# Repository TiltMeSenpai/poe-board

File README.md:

# Unnamed PoE LED Driver

## Status: UNTESTED

Hub75 LED Panel driver + 10/100 Base T to MII transciever + 25W PoE supply.  
Board is untested, estimated driver logic power consumption is ~250-500ma (hopefully less).  
Remaining 4-ish amps should be enough to drive 64x64 panel at full brightness, however, with
a 1oz copper board, this will (in theory) induce a ~20C temp rise.

## Basic Stats

| Stat | Value |
|---|---|
| Voltage  | 5v  |
| Amperage | ~5A |
| Onboard current draw | TBD (Hopefully under 500ma) |
| Interface | 10/100 base T transciever, 4 debug LED's, Hub75 header |

## Board stats

| Stat | Value |
|---|---|
| Layers             |            4 |
| Min Trace Width    |        6 mil |
| Min Trace Spacing  |        5 mil |
| Min Drill Size     |       10 mil |
| Min Via Annulus    |        5 mil |
| Min Total Via Size |       20 mil |
| Blind/Buried Vias  |           No |
| Impedence Control  |           No |
| Copper Weight      | 2 oz/Default |

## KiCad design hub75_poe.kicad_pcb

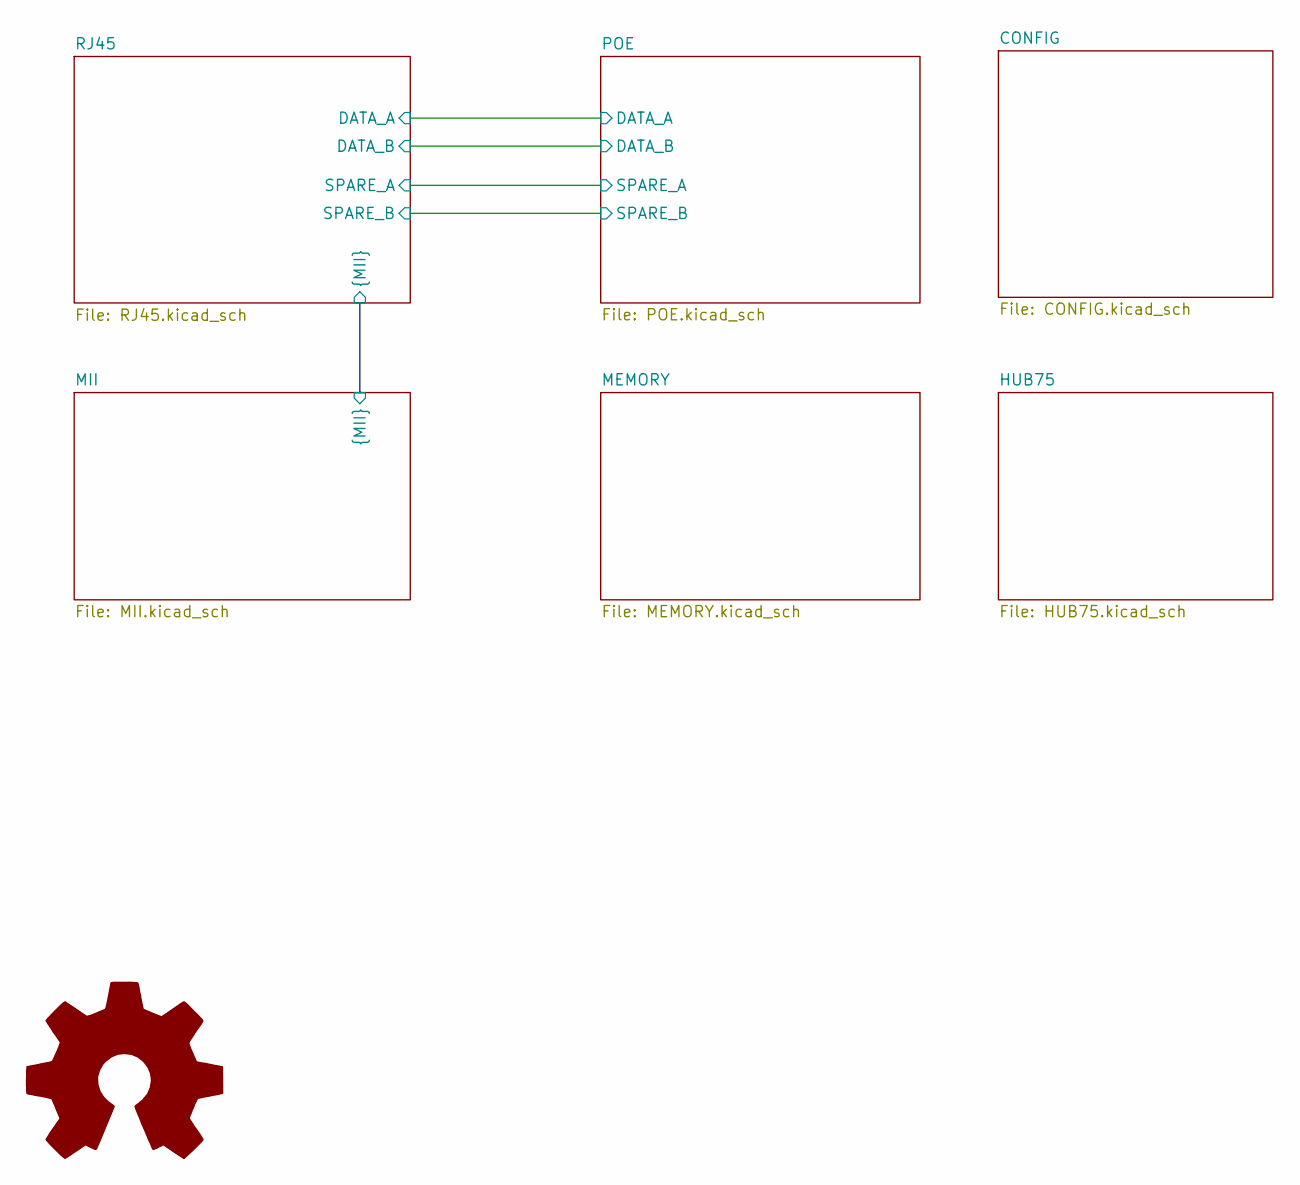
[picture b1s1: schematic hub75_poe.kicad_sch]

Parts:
S1: Logo_Open_Hardware_Large; OSHW-Symbol_6.7x6mm_SilkScreen

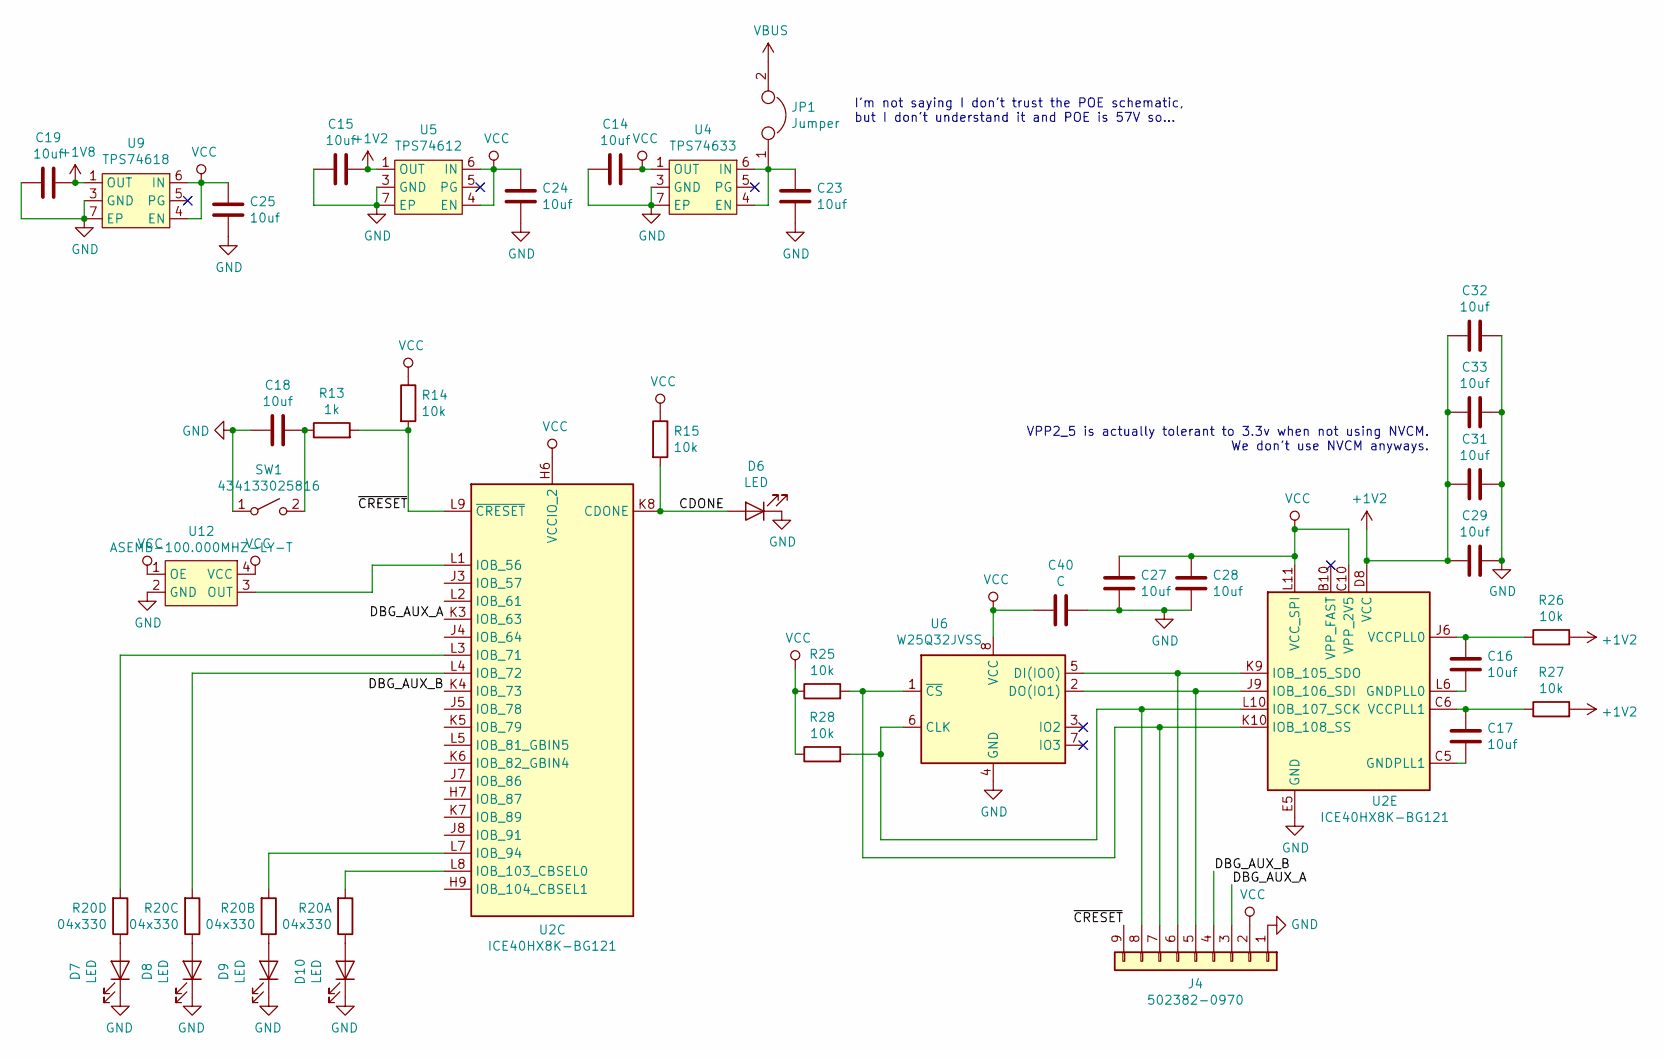
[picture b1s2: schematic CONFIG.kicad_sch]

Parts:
C14, C15, C16, C17, C19, C23, C24, C25, C27, C28, C29, C31, C32, C33: 10uf; C_0402_1005Metric
C18: 10uf; C_0805_2012Metric
C40: C; C_0402_1005Metric
D6, D7, D8, D9, D10: LED; D_0805_2012Metric_Castellated
J4: 502382-0970; Molex_CLIK-Mate_502382-0970_1x09-1MP_P1.25mm_Vertical
JP1: Jumper; PinSocket_1x02_P1.27mm_Vertical
R13: 1k; R_0402_1005Metric
R14, R15, R25, R26, R27, R28: 10k; R_0402_1005Metric
R20: 04x330; R_Array_Convex_4x0612
SW1: 434133025816; SW_Push_1P1T_NO_Vertical_Wuerth_434133025816
U2: ICE40HX8K-BG121; BGA-121_9.0x9.0mm_Layout11x11_P0.8mm_Ball0.4mm_Pad0.35mm_NS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
U4: TPS74633; WSON-6-1EP_2x2mm_P0.65mm_EP1x1.6mm
U5: TPS74612; WSON-6-1EP_2x2mm_P0.65mm_EP1x1.6mm
U6: W25Q32JVSS; SOIC-8_5.23x5.23mm_P1.27mm
U9: TPS74618; WSON-6-1EP_2x2mm_P0.65mm_EP1x1.6mm
U12: ASEMB-100.000MHZ-LY-T; SOIC-4

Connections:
+1V2: C15.2, C29.1, C31.1, C32.1, C33.1, R26.2, R27.2, U2.D4 (VCC), U2.D8 (VCC), U2.H4 (VCC), U2.H8 (VCC), U5.1 (OUT)
+1V8: C19.2, U9.1 (OUT); also elsewhere on the board
/CONFIG/CDONE: D6.2 (A), R15.2, U2.K8 (CDONE)
/CONFIG/DBG_AUX_A: J4.3, U2.K3 (IOB_63)
/CONFIG/DBG_AUX_B: J4.4, U2.K4 (IOB_73)
/CONFIG/~CRESET: J4.9, R13.2, R14.2, U2.L9 (~CRESET)
GND: C14.1, C15.1, C18.1, C19.1, C23.2, C24.2, C25.2, C27.1, C28.1, C29.2, C31.2, C32.2, C33.2, C40.2, D6.1 (K), D7.1 (K), D8.1 (K), D9.1 (K), D10.1 (K), J4.1, SW1.1 (A), U2.E5 (GND), U2.E6 (GND), U2.E7 (GND), U2.F5 (GND), U2.F6 (GND), U2.F7 (GND), U2.G5 (GND), U2.G6 (GND), U2.G7 (GND), U2.H5 (GND), U4.3 (GND), U4.7 (EP), U5.3 (GND), U5.7 (EP), U6.4 (GND), U9.3 (GND), U9.7 (EP), U12.2 (GND); also elsewhere on the board
unnamed: C16.1, R26.1, U2.J6 (VCCPLL0)
unnamed: C16.2, U2.L6 (GNDPLL0)
unnamed: C17.1, R27.1, U2.C6 (VCCPLL1)
unnamed: C17.2, U2.C5 (GNDPLL1)
unnamed: C18.2, R13.1, SW1.2 (B)
unnamed: C23.1, JP1.1, U4.4 (EN), U4.6 (IN)
unnamed: D7.2 (A), R20.5
unnamed: D8.2 (A), R20.6
unnamed: D9.2 (A), R20.7
unnamed: D10.2 (A), R20.8
unnamed: J4.5, U2.J9 (IOB_106_SDI), U6.2 (DO(IO1))
unnamed: J4.6, U2.K9 (IOB_105_SDO), U6.5 (DI(IO0))
unnamed: J4.7, R25.2, U2.K10 (IOB_108_SS), U6.1 (~CS)
unnamed: J4.8, R28.2, U2.L10 (IOB_107_SCK), U6.6 (CLK)
unnamed: R20.1, U2.L8 (IOB_103_CBSEL0)
unnamed: R20.2, U2.L7 (IOB_94)
unnamed: R20.3, U2.L4 (IOB_72)
unnamed: R20.4, U2.L3 (IOB_71)
unnamed: U2.L1 (IOB_56), U12.3 (OUT)
VBUS: JP1.2; also elsewhere on the board
VCC: C14.2, C24.1, C25.1, C27.2, C28.2, C40.1, J4.2, R14.1, R15.1, R25.1, R28.1, U2.C10 (VPP_2V5), U2.H6 (VCCIO_2), U2.L11 (VCC_SPI), U4.1 (OUT), U5.4 (EN), U5.6 (IN), U6.8 (VCC), U9.4 (EN), U9.6 (IN), U12.1 (OE), U12.4 (VCC); also elsewhere on the board

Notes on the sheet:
I'm not saying I don't trust the POE schematic, but I don't understand it and POE is 57V so...
VPP2_5 is actually tolerant to 3.3v when not using NVCM. We don't use NVCM anyways.

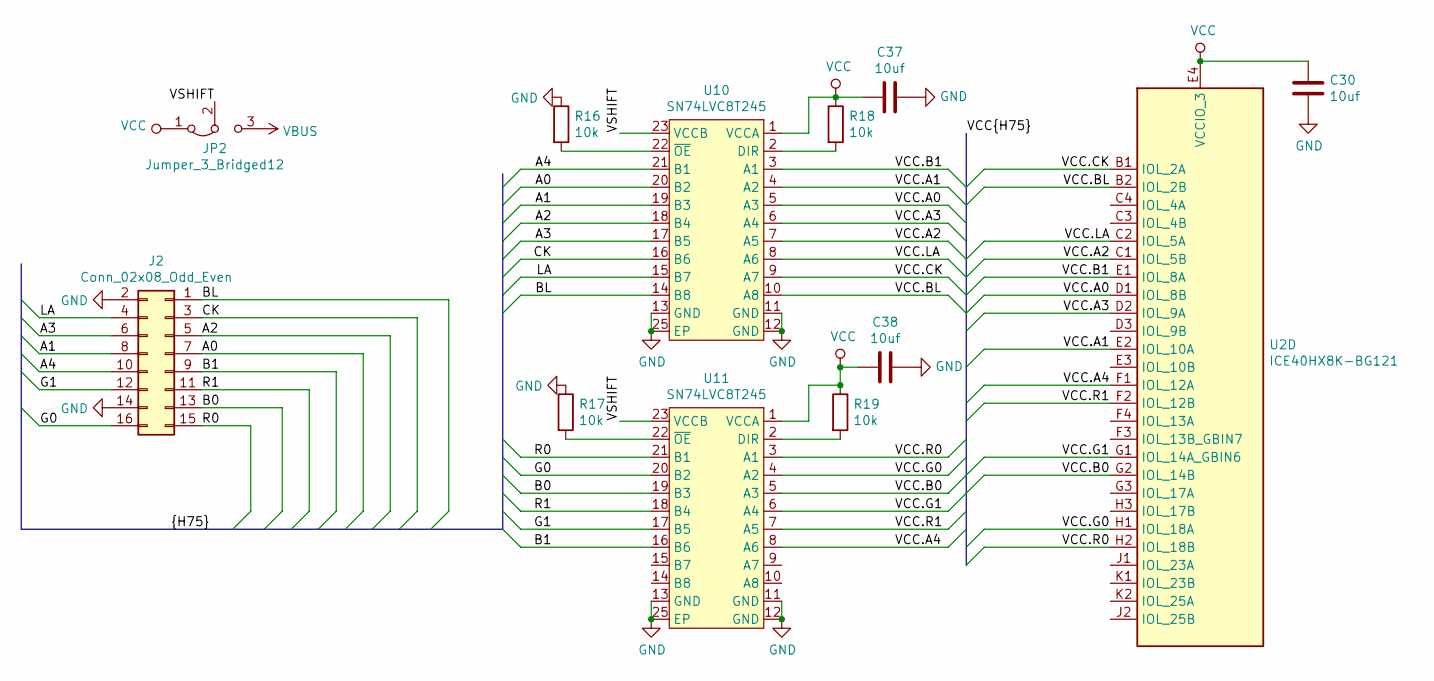
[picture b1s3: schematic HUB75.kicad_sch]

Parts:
C30, C37, C38: 10uf; C_0402_1005Metric
J2: Conn_02x08_Odd_Even; PinSocket_2x08_P2.54mm_Vertical
JP2: Jumper_3_Bridged12; PinHeader_1x03_P1.27mm_Vertical
R16, R17, R18, R19: 10k; R_0402_1005Metric
U2: ICE40HX8K-BG121; BGA-121_9.0x9.0mm_Layout11x11_P0.8mm_Ball0.4mm_Pad0.35mm_NS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
U10, U11: SN74LVC8T245

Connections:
/HUB75/A0: J2.7, U10.20 (B2)
/HUB75/A1: J2.8, U10.19 (B3)
/HUB75/A2: J2.5, U10.18 (B4)
/HUB75/A3: J2.6, U10.17 (B5)
/HUB75/A4: J2.10, U10.21 (B1)
/HUB75/B0: J2.13, U11.19 (B3)
/HUB75/B1: J2.9, U11.16 (B6)
/HUB75/BL: J2.1, U10.14 (B8)
/HUB75/CK: J2.3, U10.16 (B6)
/HUB75/G0: J2.16, U11.20 (B2)
/HUB75/G1: J2.12, U11.17 (B5)
/HUB75/LA: J2.4, U10.15 (B7)
/HUB75/R0: J2.15, U11.21 (B1)
/HUB75/R1: J2.11, U11.18 (B4)
/HUB75/VCC.A0: U2.D1 (IOL_8B), U10.5 (A3)
/HUB75/VCC.A1: U2.E2 (IOL_10A), U10.4 (A2)
/HUB75/VCC.A2: U2.C1 (IOL_5B), U10.7 (A5)
/HUB75/VCC.A3: U2.D2 (IOL_9A), U10.6 (A4)
/HUB75/VCC.A4: U2.F1 (IOL_12A), U11.8 (A6)
/HUB75/VCC.B0: U2.G2 (IOL_14B), U11.5 (A3)
/HUB75/VCC.B1: U2.E1 (IOL_8A), U10.3 (A1)
/HUB75/VCC.BL: U2.B2 (IOL_2B), U10.10 (A8)
/HUB75/VCC.CK: U2.B1 (IOL_2A), U10.9 (A7)
/HUB75/VCC.G0: U2.H1 (IOL_18A), U11.4 (A2)
/HUB75/VCC.G1: U2.G1 (IOL_14A_GBIN6), U11.6 (A4)
/HUB75/VCC.LA: U2.C2 (IOL_5A), U10.8 (A6)
/HUB75/VCC.R0: U2.H2 (IOL_18B), U11.3 (A1)
/HUB75/VCC.R1: U2.F2 (IOL_12B), U11.7 (A5)
/HUB75/VSHIFT: JP2.2 (C), U10.23 (VCCB), U10.24 (VCCB), U11.23 (VCCB), U11.24 (VCCB)
GND: C30.2, C37.2, C38.2, J2.2, J2.14, R16.1, R17.1, U10.11 (GND), U10.12 (GND), U10.13 (GND), U10.25 (EP), U11.11 (GND), U11.12 (GND), U11.13 (GND), U11.25 (EP); also elsewhere on the board
unnamed: R16.2, U10.22 (~OE)
unnamed: R17.2, U11.22 (~OE)
unnamed: R18.2, U10.2 (DIR)
unnamed: R19.2, U11.2 (DIR)
VBUS: JP2.3 (B); also elsewhere on the board
VCC: C30.1, C37.1, C38.1, JP2.1 (A), R18.1, R19.1, U2.E4 (VCCIO_3), U2.G4 (VCCIO_3), U10.1 (VCCA), U11.1 (VCCA); also elsewhere on the board

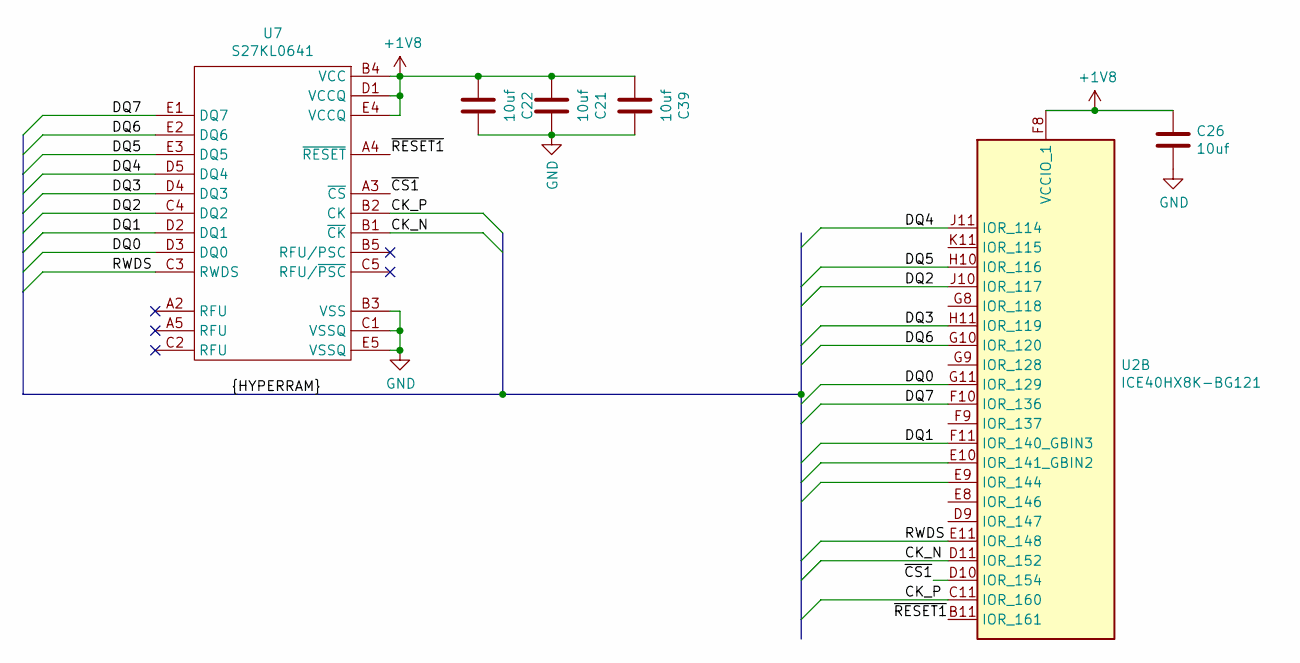
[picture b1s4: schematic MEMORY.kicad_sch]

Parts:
C21, C22, C26, C39: 10uf; C_0402_1005Metric
U2: ICE40HX8K-BG121; BGA-121_9.0x9.0mm_Layout11x11_P0.8mm_Ball0.4mm_Pad0.35mm_NS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
U7: S27KL0641; BGA-24_5x5_6.0x8.0mm

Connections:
+1V8: C21.1, C22.1, C26.1, C39.1, U2.F8 (VCCIO_1), U7.B4 (VCC), U7.D1 (VCCQ), U7.E4 (VCCQ); also elsewhere on the board
/MEMORY/CK_N: U2.D11 (IOR_152), U7.B1 (~CK)
/MEMORY/CK_P: U2.C11 (IOR_160), U7.B2 (CK)
/MEMORY/DQ0: U2.G11 (IOR_129), U7.D3 (DQ0)
/MEMORY/DQ1: U2.F11 (IOR_140_GBIN3), U7.D2 (DQ1)
/MEMORY/DQ2: U2.J10 (IOR_117), U7.C4 (DQ2)
/MEMORY/DQ3: U2.H11 (IOR_119), U7.D4 (DQ3)
/MEMORY/DQ4: U2.J11 (IOR_114), U7.D5 (DQ4)
/MEMORY/DQ5: U2.H10 (IOR_116), U7.E3 (DQ5)
/MEMORY/DQ6: U2.G10 (IOR_120), U7.E2 (DQ6)
/MEMORY/DQ7: U2.F10 (IOR_136), U7.E1 (DQ7)
/MEMORY/RWDS: U2.E11 (IOR_148), U7.C3 (RWDS)
/MEMORY/~CS1: U2.D10 (IOR_154), U7.A3 (~CS)
/MEMORY/~RESET1: U2.B11 (IOR_161), U7.A4 (~RESET)
GND: C21.2, C22.2, C26.2, C39.2, U7.B3 (VSS), U7.C1 (VSSQ), U7.E5 (VSSQ); also elsewhere on the board

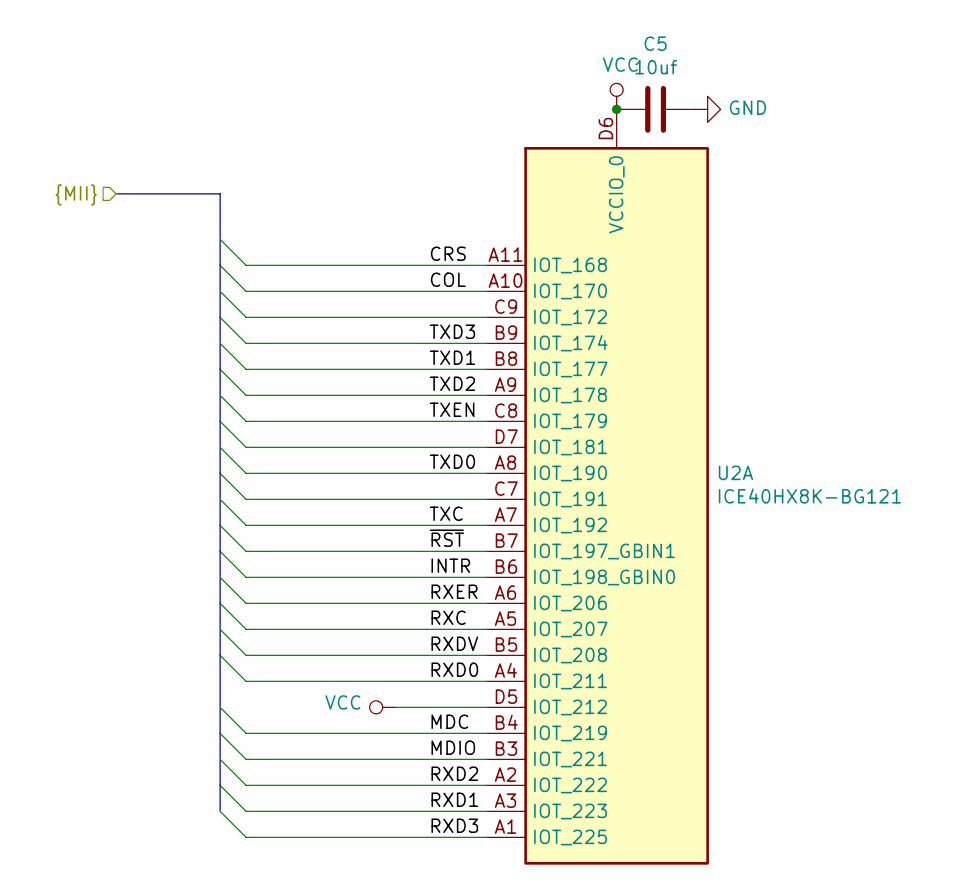
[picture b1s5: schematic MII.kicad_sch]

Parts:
C5: 10uf; C_0402_1005Metric
U2: ICE40HX8K-BG121; BGA-121_9.0x9.0mm_Layout11x11_P0.8mm_Ball0.4mm_Pad0.35mm_NS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

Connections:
/COL: U2.A10 (IOT_170); also elsewhere on the board
/CRS: U2.A11 (IOT_168); also elsewhere on the board
/INTR: U2.B6 (IOT_198_GBIN0); also elsewhere on the board
/MDC: U2.B4 (IOT_219); also elsewhere on the board
/MDIO: U2.B3 (IOT_221); also elsewhere on the board
/RXC: U2.A5 (IOT_207); also elsewhere on the board
/RXD0: U2.A4 (IOT_211); also elsewhere on the board
/RXD1: U2.A3 (IOT_223); also elsewhere on the board
/RXD2: U2.A2 (IOT_222); also elsewhere on the board
/RXD3: U2.A1 (IOT_225); also elsewhere on the board
/RXDV: U2.B5 (IOT_208); also elsewhere on the board
/RXER: U2.A6 (IOT_206); also elsewhere on the board
/TXC: U2.A7 (IOT_192); also elsewhere on the board
/TXD0: U2.A8 (IOT_190); also elsewhere on the board
/TXD1: U2.B8 (IOT_177); also elsewhere on the board
/TXD2: U2.A9 (IOT_178); also elsewhere on the board
/TXD3: U2.B9 (IOT_174); also elsewhere on the board
/TXEN: U2.C8 (IOT_179); also elsewhere on the board
/~RST: U2.B7 (IOT_197_GBIN1); also elsewhere on the board
GND: C5.2; also elsewhere on the board
VCC: C5.1, U2.D5 (IOT_212), U2.D6 (VCCIO_0); also elsewhere on the board

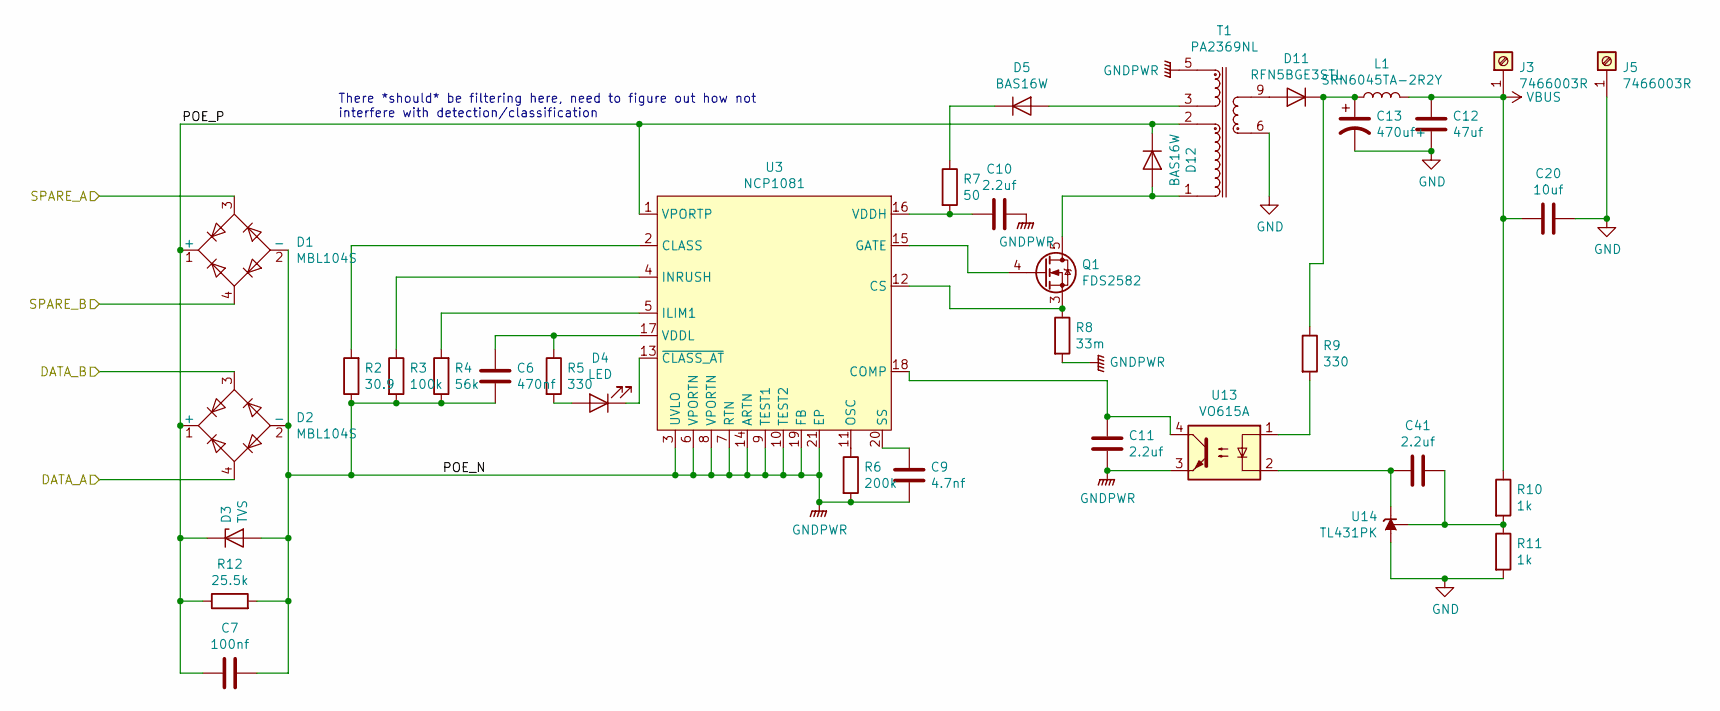
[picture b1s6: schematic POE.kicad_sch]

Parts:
C6: 470nf; C_0402_1005Metric
C7: 100nf; C_0805_2012Metric
C9: 4.7nf; C_0402_1005Metric
C10, C11, C41: 2.2uf; C_0402_1005Metric
C12: 47uf; C_0805_2012Metric
C13: 470uf+; CP_Elec_8x10
C20: 10uf; C_0805_2012Metric
D1, D2: MBL104S; Diode_Bridge_Vishay_MBLS
D3: TVS; D_SMA
D4: LED; D_0805_2012Metric_Castellated
D5, D12: BAS16W; SOT-323_SC-70
D11: RFN5BGE3STL; TO-252-2
J3, J5: 7466003R
L1: SRN6045TA-2R2Y; L_Bourns_SRN6045TA
Q1: FDS2582; SOP-8_3.9x4.9mm_P1.27mm
R2: 30.9; R_0402_1005Metric
R3: 100k; R_0402_1005Metric
R4: 56k; R_0402_1005Metric
R5, R9: 330; R_0402_1005Metric
R6: 200k; R_0402_1005Metric
R7: 50; R_0402_1005Metric
R8: 33m; R_2512_6332Metric
R10, R11: 1k; R_0402_1005Metric
R12: 25.5k; R_0805_2012Metric
T1: PA2369NL
U3: NCP1081; HTSSOP-20-1EP_4.4x6.5mm_P0.65mm_EP3.4x6.5mm
U13: VO615A; VO615A-9X017T
U14: TL431PK; SOT-89-3

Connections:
/DATA_A: D2.4 (~~); also elsewhere on the board
/DATA_B: D2.3 (~~); also elsewhere on the board
/POE/POE_P: C7.1, D1.1 (+), D2.1 (+), D3.1 (A1), D12.3 (K), R12.1, T1.2, U3.1 (VPORTP)
/SPARE_A: D1.3 (~~); also elsewhere on the board
/SPARE_B: D1.4 (~~); also elsewhere on the board
GND: C12.2, C13.2, C20.2, J5.1, R11.2, T1.6, T1.7, U14.2 (A); also elsewhere on the board
GNDPWR: C6.2, C7.2, C9.2, C10.2, C11.2, D1.2 (-), D2.2 (-), D3.2 (A2), R2.1, R3.2, R4.1, R6.2, R8.2, R12.2, T1.5, U3.3 (UVLO), U3.6 (VPORTN), U3.7 (RTN), U3.8 (VPORTN), U3.9 (TEST1), U3.10 (TEST2), U3.14 (ARTN), U3.19 (FB), U3.21 (EP), U13.3; also elsewhere on the board
unnamed: C6.1, R5.1, U3.17 (VDDL)
unnamed: C9.1, U3.20 (SS)
unnamed: C10.1, R7.2, U3.16 (VDDH)
unnamed: C11.1, U3.18 (COMP), U13.4
unnamed: C13.1, D11.2 (K), L1.1, R9.1
unnamed: C41.1, U13.2, U14.3 (K)
unnamed: C41.2, R10.2, R11.1, U14.1 (REF)
unnamed: D4.1 (K), U3.13 (~CLASS_AT)
unnamed: D4.2 (A), R5.2
unnamed: D5.1 (A), T1.3
unnamed: D5.3 (K), R7.1
unnamed: D11.1 (A), D11.3 (A), T1.9, T1.10
unnamed: D12.1 (A), Q1.5 (D), Q1.6 (D), Q1.7 (D), Q1.8 (D), T1.1
unnamed: Q1.1 (S), Q1.2 (S), Q1.3 (S), R8.1, U3.12 (CS)
unnamed: Q1.4 (G), U3.15 (GATE)
unnamed: R2.2, U3.2 (CLASS)
unnamed: R3.1, U3.4 (INRUSH)
unnamed: R4.2, U3.5 (ILIM1)
unnamed: R6.1, U3.11 (OSC)
unnamed: R9.2, U13.1
VBUS: C12.1, C20.1, J3.1, L1.2, R10.1; also elsewhere on the board

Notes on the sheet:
There *should* be filtering here, need to figure out how not interfere with detection/classification

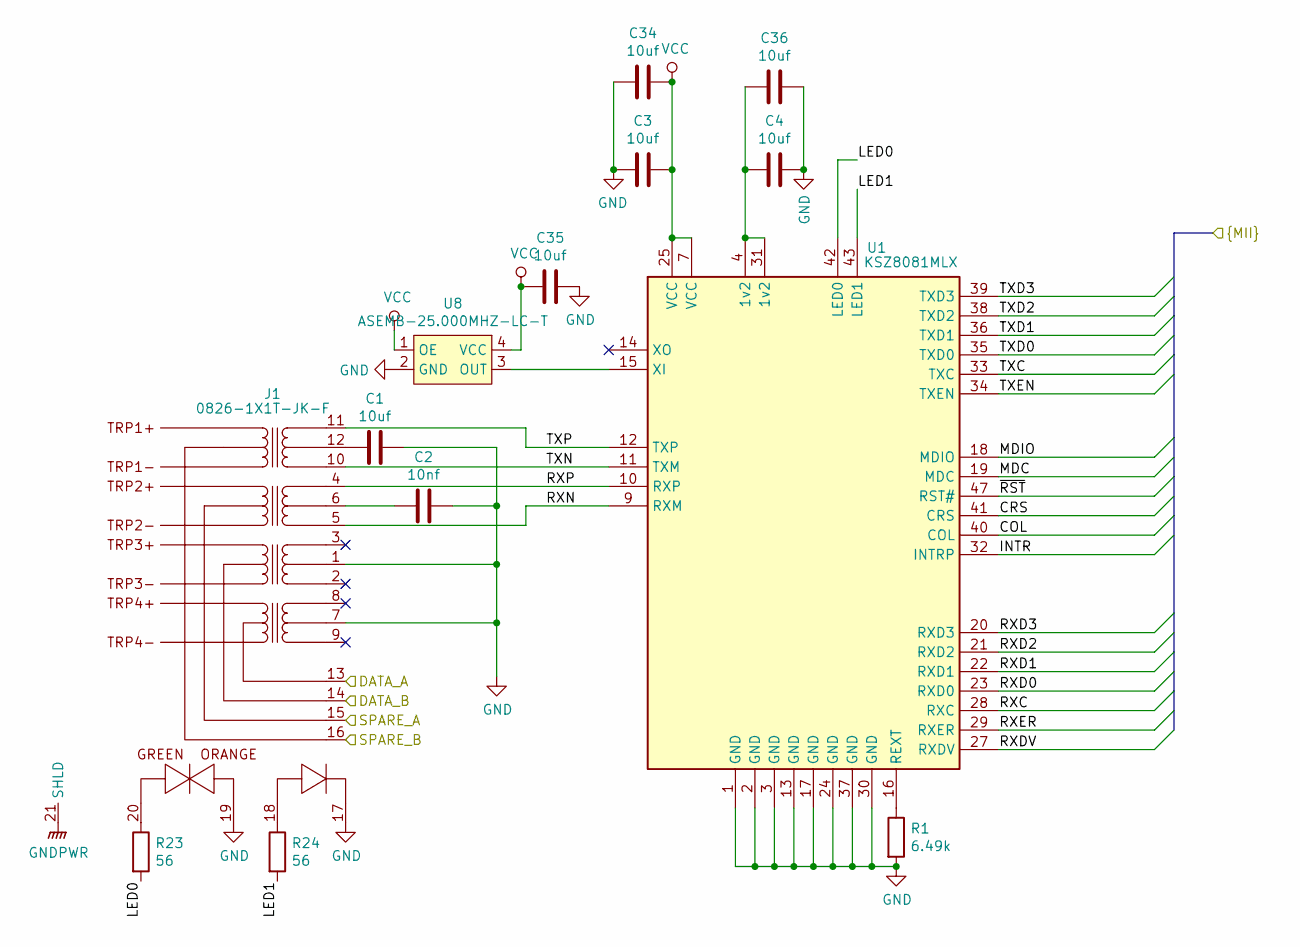
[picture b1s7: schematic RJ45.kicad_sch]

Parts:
C1: 10uf; C_0805_2012Metric
C2: 10nf; C_0805_2012Metric
C3, C4, C34, C35, C36: 10uf; C_0402_1005Metric
J1: 0826-1X1T-JK-F; 08261X1TGHF
R1: 6.49k; R_0402_1005Metric
R23, R24: 56; R_0402_1005Metric
U1: KSZ8081MLX; LQFP-48_7x7mm_P0.5mm
U8: ASEMB-25.000MHZ-LC-T; SOIC-4

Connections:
/COL: U1.40 (COL); also elsewhere on the board
/CRS: U1.41 (CRS); also elsewhere on the board
/DATA_A: J1.13; also elsewhere on the board
/DATA_B: J1.14; also elsewhere on the board
/INTR: U1.32 (INTRP); also elsewhere on the board
/MDC: U1.19 (MDC); also elsewhere on the board
/MDIO: U1.18 (MDIO); also elsewhere on the board
/RJ45/LED0: R23.2, U1.42 (LED0)
/RJ45/LED1: R24.2, U1.43 (LED1)
/RJ45/RXN: J1.5, U1.9 (RXM)
/RJ45/RXP: J1.4, U1.10 (RXP)
/RJ45/TXN: J1.10, U1.11 (TXM)
/RJ45/TXP: J1.11, U1.12 (TXP)
/RXC: U1.28 (RXC); also elsewhere on the board
/RXD0: U1.23 (RXD0); also elsewhere on the board
/RXD1: U1.22 (RXD1); also elsewhere on the board
/RXD2: U1.21 (RXD2); also elsewhere on the board
/RXD3: U1.20 (RXD3); also elsewhere on the board
/RXDV: U1.27 (RXDV); also elsewhere on the board
/RXER: U1.29 (RXER); also elsewhere on the board
/SPARE_A: J1.15; also elsewhere on the board
/SPARE_B: J1.16; also elsewhere on the board
/TXC: U1.33 (TXC); also elsewhere on the board
/TXD0: U1.35 (TXD0); also elsewhere on the board
/TXD1: U1.36 (TXD1); also elsewhere on the board
/TXD2: U1.38 (TXD2); also elsewhere on the board
/TXD3: U1.39 (TXD3); also elsewhere on the board
/TXEN: U1.34 (TXEN); also elsewhere on the board
/~RST: U1.47 (RST#); also elsewhere on the board
GND: C1.2, C2.2, C3.2, C4.2, C34.2, C35.2, C36.2, J1.1, J1.7, J1.17, J1.19, R1.2, U1.1 (GND), U1.2 (GND), U1.3 (GND), U1.13 (GND), U1.17 (GND), U1.24 (GND), U1.30 (GND), U1.37 (GND), U8.2 (GND); also elsewhere on the board
GNDPWR: J1.21 (SHLD), J1.22 (SHLD); also elsewhere on the board
unnamed: C1.1, J1.12
unnamed: C2.1, J1.6
unnamed: C4.1, C36.1, U1.4 (1v2), U1.31 (1v2)
unnamed: J1.18, R24.1
unnamed: J1.20, R23.1
unnamed: R1.1, U1.16 (REXT)
unnamed: U1.15 (XI), U8.3 (OUT)
VCC: C3.1, C34.1, C35.1, U1.7 (VCC), U1.25 (VCC), U8.1 (OE), U8.4 (VCC); also elsewhere on the board

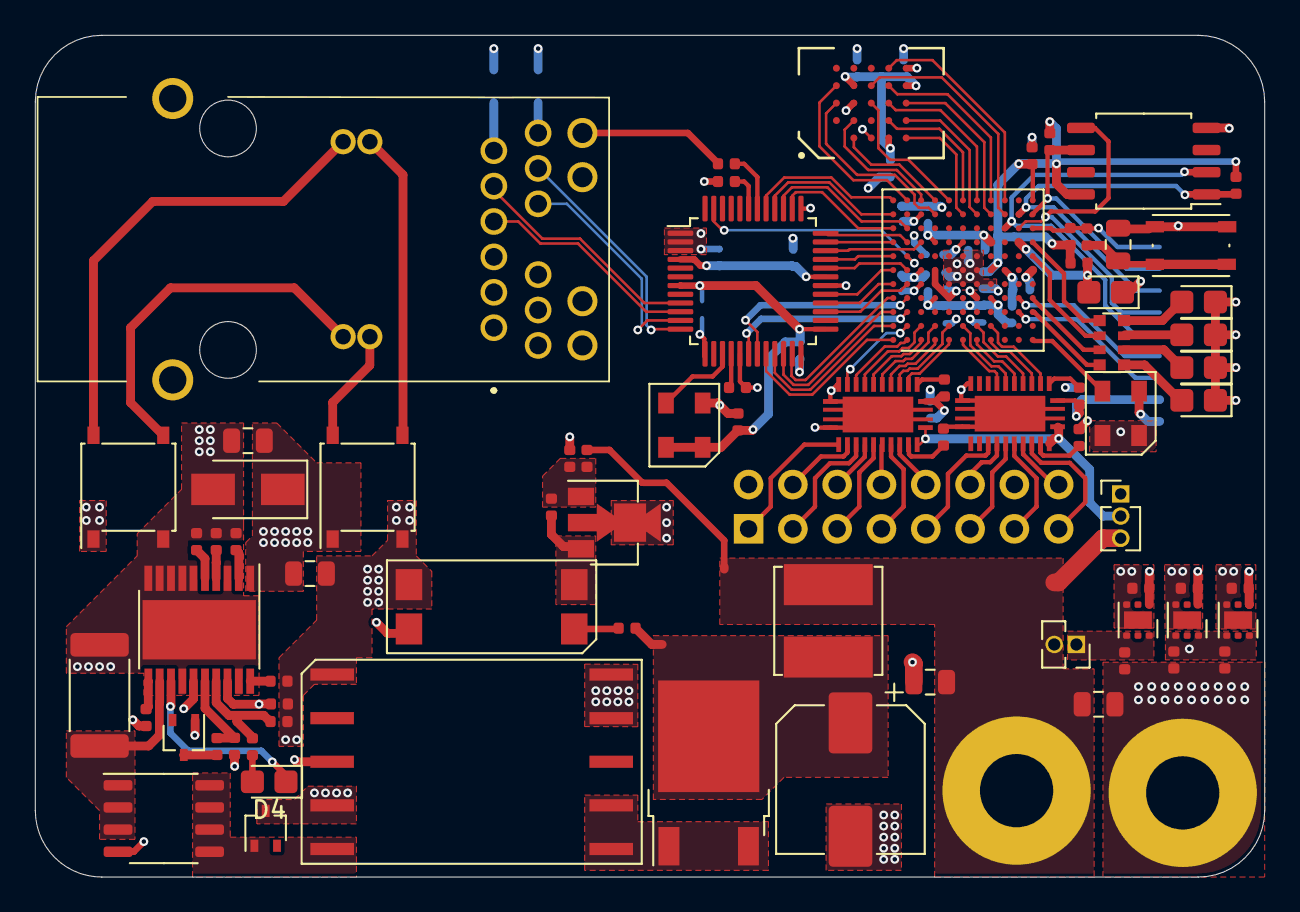
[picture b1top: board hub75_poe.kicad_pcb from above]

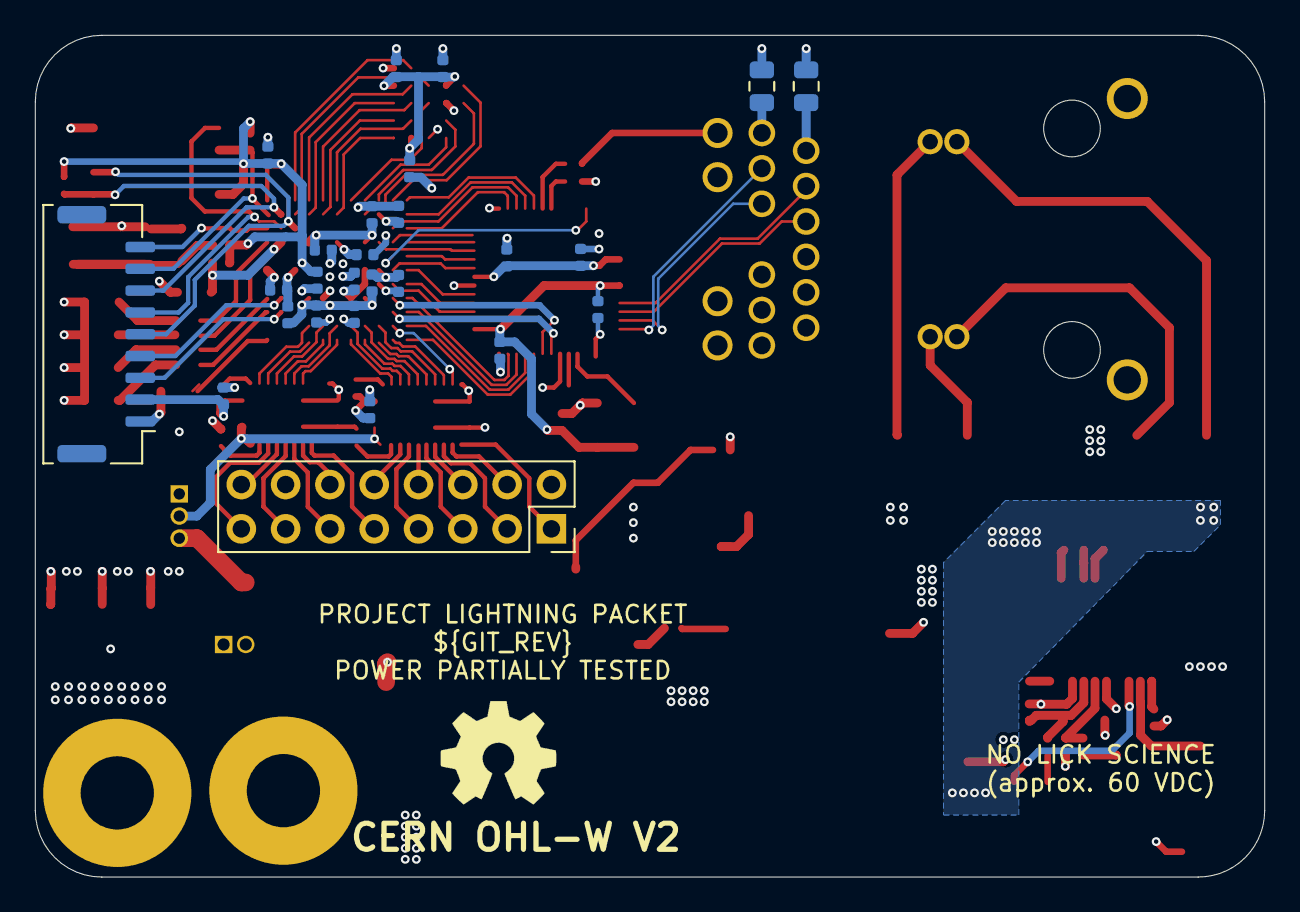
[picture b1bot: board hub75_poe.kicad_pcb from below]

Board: 4 copper layers, 70.5 x 48.3 mm, 104 parts (27 on the bottom side), 132 nets.

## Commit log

2020-05-26 Init
2020-05-26 Edit README.md
2020-05-26 Fix table (for real?)
2020-06-02 Routing changes, pullups, etc
2020-06-03 Routing cleanup, fix primary transformer
2020-06-12 Change PoE controller to NCP1081
2020-06-14 Update routing and icons/text
2020-06-15 Add missing detection resistor
2020-06-25 Add gitlab CI runner
2020-06-25 Fix script submodule url
2020-06-25 Make build script executable
2020-06-25 Specify python 3
2020-06-25 More routing cleanup
2020-06-26 Fix SOT-89-3 footprint
2020-06-26 Change version format to tag+commit
2020-06-26 Move plot scripts to docker container
2020-06-26 Fix environment variables in .gitlab_ci.yml
2020-06-26 Change gerber plot invocation
2020-07-02 Swap low voltage caps, remove hv side LC filter
2020-07-02 Add transformer snubber diode
2020-07-02 Change tag in .gitlab-ci.yml to "latest"
2020-07-05 Move snubber diode to board front
2020-07-14 Initial Github Action workflow
2020-07-14 Add @dev ref to plot-gerbers step

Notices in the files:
hub75_poe.kicad_pcb:
CERN OHL-W V2
